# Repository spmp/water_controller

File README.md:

Water Controller
================

The aim of this project is to control and monitor a water heating system.
This is currently a **Work in Progress**, and it is largely incomplete.

The project will consist of four main parts:

  1. An atmega328 MCU with a control system that directly interfaces with
     the water heater. It also operates over a serial interface to interact
     with a PC.

  2. A daemon running on the PC which can talk to the MCU. The daemon receives
     regular logging information from the MCU which it saves to a database.
     The daemon also allows various commands to be sent to the MCU.

  3. A web application that can display logs from the database, and can
     control the MCU via the daemon.
     
  4. A schematic and PCB artwork.

Currently only (1) is functional.

The _driveres_ for the project are in `AVR-lib`. At this stage I am (slowly) moving to github for issue tracking etc.

MCU
---

The project uses the Arduino Nano for both prototyping and target operation. To upload the code do the following:

 1. Plug in the MCU via USB to your computer. Check that `lsusb` shows the
    device, and that /dev/ttyUSB0 is writable (add your user to that device's
    group if not).

 2. Install the avr gcc toolchain. In Ubuntu/Debian, the packages you need
    (at least) are `avr-gcc`, `avr-libc`, and `avrdude` and their
    dependencies.

 3. Run `make` to compile the source, and `make upload` to compile and upload
    to the MCU via `/dev/ttyUSB*`. The program will start running immediately.

At present, the MCU reads data from the following inputs:

 * Pressure sensor (MPXV4006 I think...) via 12 bit I2C ADC (MPXV4006)
 * Temperature sensors (DS18B20) via OW to I2C (DS2482-100) (WIP)

These are sent over the serial interface to the PC along with a "timestamp" (the
number of seconds since the program started) at regular intervals.

To view the output, run `screen /dev/ttyUSB0 38400` (exit with `C-a k y`).

Logging daemon (logger.py)
--------------------------

This saves the data sent from the MCU to a sqlite3 database. Written in
Python3. To run it, just run

    $ ./logger.py

when the MCU is connected to the computer. The program will print out the
messages it recieves from the MCU, and also insert them into the database
`log_timeseries.db`. Type `Ctrl-C` or `Ctrl-D` to exit. You can view the
database directly using `sqlite3 log_timerseries.db`.

The logger should also have an interface for sending commands to the MCU. The
interface will be over TCP or a named pipe.

Web interface
-------------

The backend of the web layer reads from the sqlite3 database and displays
useful graphs on a web page. The graphs are rendered client-side using
jqplot, a jquery plugin. All of the javascript libraries are accessed over
cdn, meaning they don't have to be stored on the web server.

The backend is written in Python3, and uses the [Bottle web framework][bottle].
Bottle is a WSGI compliant framework, so it can be used with apache or nginx.
It can also run on its own using the builtin Python WSGIServer. This is the
current setup, and it can be run using

    $ web/webapp.py

where it serves the files to localhost:8080.

[bottle]: http://bottlepy.org/docs/stable/

The web page should also contain some commands to directly control the MCU.
These will be sent via the web backend to the logging daemon and from there
on to the MCU.

Circuit
-------

In brief: The Arduino nano plugs into the circuit board, reads its inputs from I2C, sending serial out via a MAX232. The heaters and pump are controlled via zero crossing triac driver and triacs. The filler solenoid is controlled via logic level fet. All outputs can be disabled, overwridden, or be controlled via MCU with a three position toggle switch. LED's indicate the output state, and the MCU flashes politely when operating. DC power is supplied by a 12V smps.

The circuit and artwork are in ```cad``` and ```eagle``` respectivly.

Issues
------
* The I2C driver needs a major upate which must happen in tandem with this (and all other dependent projects) to support a separate error state with recovery.
* If an I2C error in level is detected it must:
    1. Report 0mm
    2. Turn off heaters
    3. Turn off filler
    4. Turn off pump
    5. Raise a _level_ error flag in USART output
    
* If an error in temperature is detected it must:
    1. Report 0deg cent.
    2. Turn off heater
    3. Raise a _temperature_ error flag in USART output
    
Normal operation must continue once normal sensing is restored.

* Fill time detection and auto off. Sometimes the filler does not turn off correctl due to I2C errors or misreading. To avoid a flooded yard whilst on holiday a maximum fill time needs to be obeyed, taking into account a complete fill _with_ the pump on. If this time (`MAX_FILL_TIME`) is exceeded the filler must be disabled and not re-enabled unless done so manually via USART.

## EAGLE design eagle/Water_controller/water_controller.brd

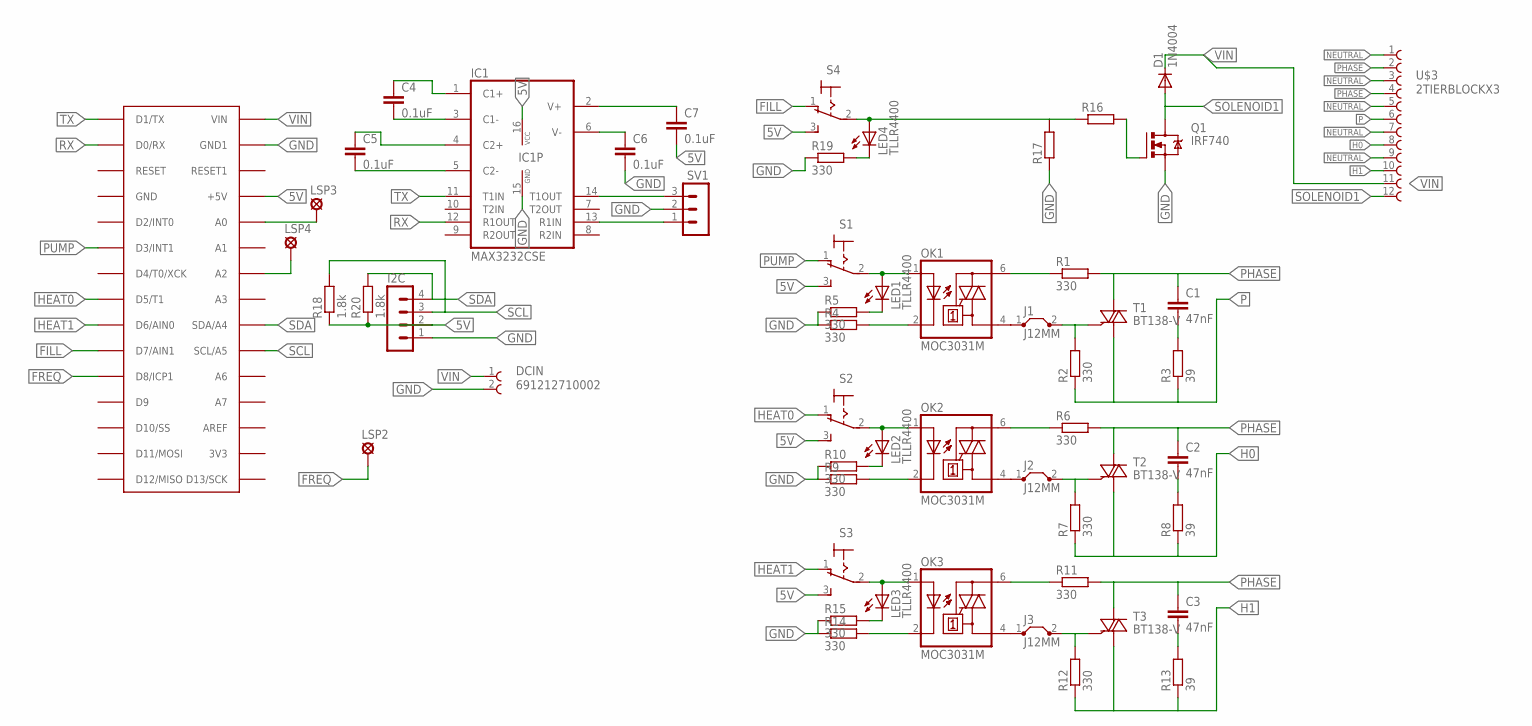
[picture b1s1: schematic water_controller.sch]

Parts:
C1, C2, C3: 47nF; C150-064X183
C4, C5, C6, C7: 0.1uF; C0805
D1: 1N4004; DO41-10
DCIN: 691212710002
I2C: MA04-1
IC1: MAX3232CSE; SO16
J1, J2, J3: J12MM; 12
LED1, LED2, LED3, LED4: TLLR4400; LED3MM
LSP2, LSP3, LSP4: LSP11
OK1, OK2, OK3: MOC3031M; DIL06; MPN MOC3063
Q1: IRF740; TO220BV
R1, R2, R6, R7, R11, R12: 330; M1206
R3, R8, R13: 39; M1206
R4, R5, R9, R10, R14, R15, R19: 330; R1206
R16: R-EU_0204/7; 0204/7
R17: R-EU_M1206; M1206
R18, R20: 1.8k; R1206
S1, S2, S3, S4: M9040P
SV1: MA03-1
T1, T2, T3: BT138-V; TO220BV
U$1: ARDUINONANO; PDIP-32
U$3: 2TIERBLOCKX3; 2TIERX3

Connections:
5V: C7.2, I2C.2, IC1.16 (VCC), R18.1, R20.1, S1.3 (S), S2.3 (S), S3.3 (S), S4.3 (S), U$1.+5V
FILL: S4.1 (O), U$1.D7 (D7/AIN1)
FREQ: LSP2.MP, U$1.D8 (D8/ICP1)
GND: C6.2, DCIN.2, I2C.1, IC1.15 (GND), Q1.S, R4.1, R5.1, R9.1, R10.1, R14.1, R15.1, R17.1, R19.1, SV1.2, U$1.GND1
H0: R7.1, R8.1, T2.T1 (A1), U$3.8
H1: R12.1, R13.1, T3.T1 (A1), U$3.10
HEAT0: S2.1 (O), U$1.D5 (D5/T1)
HEAT1: S3.1 (O), U$1.D6 (D6/AIN0)
unnamed: C1.2, R3.2
unnamed: C2.2, R8.2
unnamed: OK1.6 (A2), R1.1
unnamed: J1.2, R2.2, T1.G
unnamed: C4.2, IC1.3 (C1-)
unnamed: OK1.2 (C), R4.2
unnamed: LED1.A, OK1.1 (A), S1.2
unnamed: LED1.K (C), R5.2
unnamed: C4.1, IC1.1 (C1+)
unnamed: OK2.6 (A2), R6.1
unnamed: J2.2, R7.2, T2.G
unnamed: OK2.2 (C), R9.2
unnamed: LED2.A, OK2.1 (A), S2.2
unnamed: LED2.K (C), R10.2
unnamed: C3.2, R13.2
unnamed: OK3.6 (A2), R11.1
unnamed: J3.2, R12.2, T3.G
unnamed: OK3.2 (C), R14.2
unnamed: LED3.A, OK3.1 (A), S3.2
unnamed: LED3.K (C), R15.2
unnamed: C5.2, IC1.5 (C2-)
unnamed: Q1.G, R16.2
unnamed: C5.1, IC1.4 (C2+)
unnamed: LED4.A, R16.1, R17.2, S4.2
unnamed: LED4.K (C), R19.2
unnamed: C6.1, IC1.6 (V-)
unnamed: C7.1, IC1.2 (V+)
unnamed: J1.1, OK1.4 (A1)
unnamed: J2.1, OK2.4 (A1)
unnamed: J3.1, OK3.4 (A1)
unnamed: IC1.13 (R1IN), SV1.1
unnamed: IC1.14 (T1OUT), SV1.3
unnamed: LSP4.MP, U$1.A2
unnamed: LSP3.MP, U$1.A0
NEUTRAL: U$3.1, U$3.3, U$3.5, U$3.7, U$3.9
P: R2.1, R3.1, T1.T1 (A1), U$3.6
PHASE: C1.1, C2.1, C3.1, R1.2, R6.2, R11.2, T1.T2 (A2), T2.T2 (A2), T3.T2 (A2), U$3.2, U$3.4
PUMP: S1.1 (O), U$1.D3 (D3/INT1)
RX: IC1.12 (R1OUT), U$1.D0/RX
SCL: I2C.3, R18.2, U$1.A5 (SCL/A5)
SDA: I2C.4, R20.2, U$1.A4 (SDA/A4)
SOLENOID1: D1.A, Q1.D, U$3.12
TX: IC1.11 (T1IN), U$1.D1/TX
VIN: D1.C, DCIN.1, U$1.VIN, U$3.11

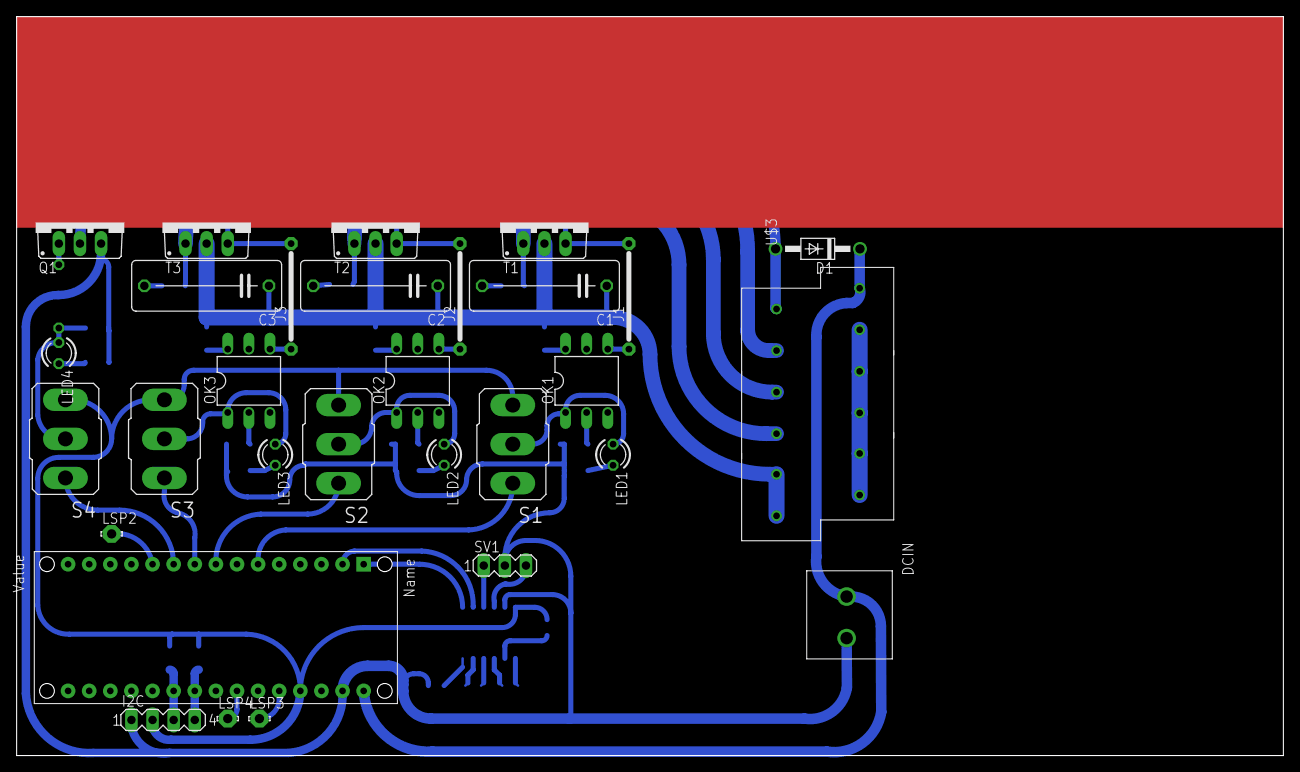
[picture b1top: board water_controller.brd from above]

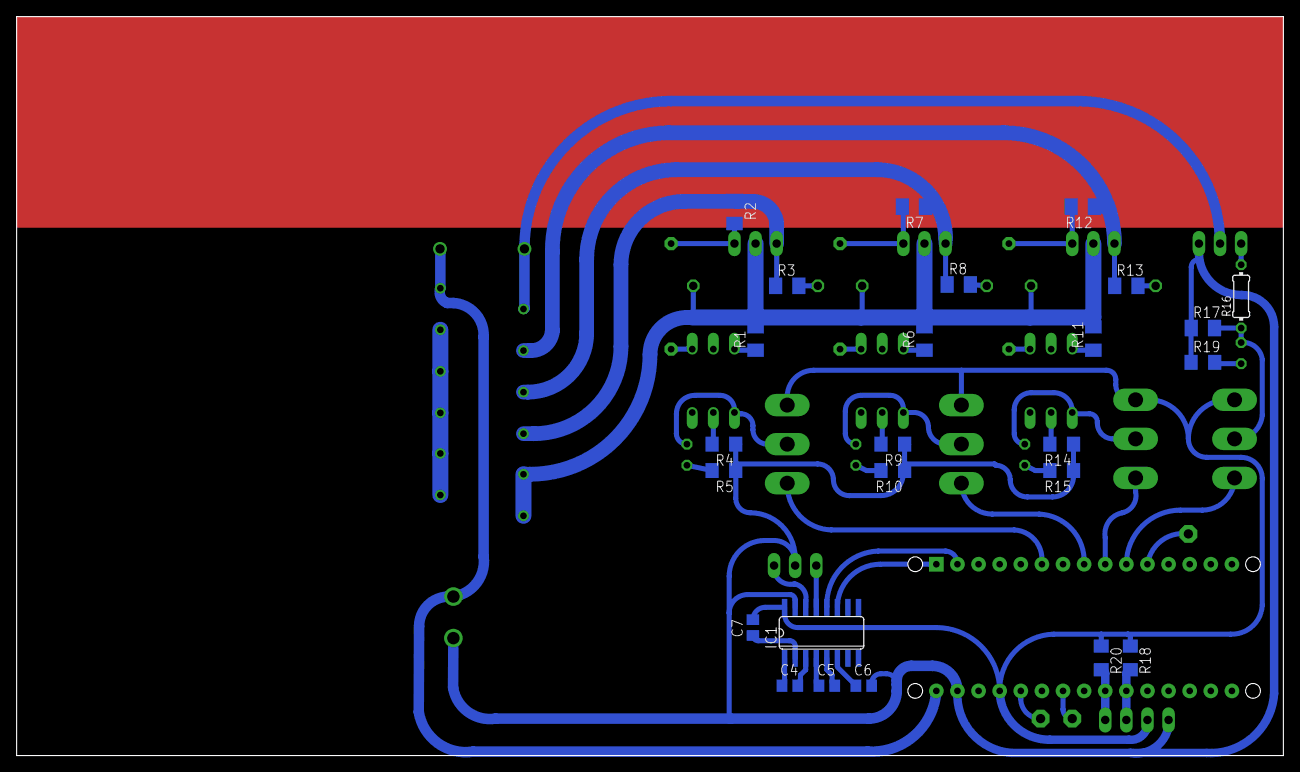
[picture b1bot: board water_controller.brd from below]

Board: 2 copper layers, 152.4 x 88.9 mm, 55 parts (25 on the bottom side), 52 nets.

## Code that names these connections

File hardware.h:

#pragma once
#include <avr/io.h>

/* AVR specifics */
#include "AVR-lib/clock.h"
#include "AVR-lib/ds18x20.h"
#include "AVR-lib/i2c_safe.h"
#include "AVR-lib/usart.h"
#include "AVR-lib/wd.h"
#include "state-machine.h"

/* DEBUGGING - i.e no environmental measurements */
// #define DEBUGGING

/* State machine defaults */
#define STATEMACHINEENABLEDONSTART 1
#define LOGGINGENABLEDONSTART 1
#define HEATERENABLEDONSTART 1
#define ANALYTICSENABLEDONSTART 1

/* Fill timer */
#define FILL_MAX_TIME 900
#define FILL_CHECK_TIME 60

/* Heater size */
#define HEATER_SIZE     2400L
#define SPECIFIC_HEAT_WATER 4186L

/* Clock and timing settings, time in 1/125's of a second*/
#define LONG_TIME_INTERVAL          CLOCK_TICKS_PER_SECOND*600L

/* Inputs */
#include "temperature.h"//Temperature reading
#include "level.h"      //Level and volume reading

/* Data buss settings   */
// USART
#define USARTBAUD       38400
// I2C
#define I2CSPEED        1000
// OW bit bang
#define OWPIN           PB0
#define OWIN            PINB
#define OWOUT           PORTB
#define OWDDR           DDRB
#define OW_USE_INTERNAL_PULLUP     0

// ds18x20 defines
#define DS18X20TEMPRES  DS18B20_12_BIT 

// IO defines:
#define ONBOARD_LED     PB5

#define OUTPUT_PORT     PORTD
#define INPUT_PORT      PIND
#define DIRECTION_REG   DDRD
#define PUMP_PIN        PD3
#define FILL_PIN        PD7
#define HEAT1_PIN       PD5
#define HEAT2_PIN       PD6

/* Initialise all hardware relevant to the project, usart, i2c, clock, external
 * sensors, Everyting!
 * One call to rule them all */
void init_hardware(struct Program *program);

/* Initialise I/O ports on the AVR */
void init_io_ports(void);

/* Hardware states */
uint8_t pump_state(void);
uint8_t fill_state(void);
uint8_t heater_state(void);

/* Set hardware states */
void pump_set(uint8_t state);
void fill_set(uint8_t state);
void heater_set(uint8_t state);

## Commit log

2013-11-02 Add clock using timer/counter 2
2013-11-02 log ultrasonic & analog inputs to serial with timestamp
2013-11-02 simplify the ultrasonic distance measure
    The ultrasonic measurer now uses a single I/O pin (PORTB0/ardiuno digital 8)
    and a single interrupt (TIMER1_CAPT). When the ultrasonic sensor is not in
    use, TIMER1 is free for use in other parts of the application.
2013-11-02 add informative README.md
2013-11-07 Add logger and basic web interface that displays graphs from the micro.
2013-11-30 Modified ADC read_analog for the case of pin 8 being internal temp. Spun off ADC stuff to adc.{c,h} Added very basic frequqncy measurement using 16 input capture timer Modified main - removed ultraso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
2013-12-08 Cleaned up as per *useful* comments. Added temperature related things. Maybe fixed frequency counter.
2014-01-14 Levels and things, usart recieve and parse. Hardware will change
2014-01-14 Tidy up recieving commands and the core program loop.
2014-01-15 Move code around mostly, having trouble compiling - multiple definition of 'read_inputs_flag'.
2014-01-20 Hardware: Schematic and PCB artwork done.
2014-02-18 i2c working with safe high level commands -- still need to find a way to break out of read_ack and read_nak while loop. Logging in separate folder. The idea of a config.h not sure how to impliment wi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
2014-02-18 Fixed dependency issues, some more stuff in command to test temperature probe.. all good. Need to get this whole struct input blah thing sorted so can get some good log messages.. Anyone want to fini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
2014-02-21 Defined two more time periods: medium and fast, set state machine to run in medium tome perod, and separated USART, statemachine and logging, such that they are indipendent and USART and logging are 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
2014-02-26 Wow, a Version 1.0alpha! Should be a working system _when_ program is populated with values... still to be done. Lots and lots to do... oh so much for a project that was supposed to take two weeks. N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
2014-03-03 A working version with no 'state machine' for now. Added new functions to usart for uint32 and half uint32. Changed uint and i2c_safe init such that speed/baude and f_cpu are parameters. Changed the 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
2014-03-03 loads of floating point stuff sorted, volume and level fixed with zeroing routine. Fill routine faulty. redo with a ton of if thens
2014-03-06 Stuff, and the attempt to have multiple programs as program[], failing to initialise the programs so will revert on the next commit. Floating point done. Progmem done, hence USART menu (command.c) do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
2014-08-12 Fixing broken heater logic. Clunky but obvious code
2014-08-13 fixed a lot of the temperature and heating stuff. Linearly approximating volume to avoid floating point
2014-08-13 Test of various level/volume/heating related stuff.
2014-08-15 moving to another computer. Need to fix probe.. again
2014-08-18 Added basic morning fill logic. Updated I2C address of one temperature sensor
2014-08-19 moving from BaaBaaBlacksheep for level testing
2014-08-19 Recalibrate level sensor, revert Volume to floating point version
2014-09-08 BaaBaaBlacksheep: Add watchdog initialisation and reset (after logging message). Add initialisation serial string.
2014-09-08 Attempting to fix watchdog lockout
2014-09-10 added prefix's and suffixes to command.c usart output. Code is HORRID and needs to be written nicely some time in the future- reuse etc..
2014-09-10 Fixed overflow in temperature by increasing size of read_AT30TSE758 to int32, whilst keeping temperature at uint16 as assue its not negative. Note there is a multiplication by 125 in read_AT30TSE758,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
2014-10-08 Dunno where, from BaaBaa
2014-10-08 Rudimentary watchdog reset after 4S implimented. Added variable 'mcusr_mirror' in attempt to catch reset source, not working, or else always 0
2014-10-09 Added proper reset testing using Optiboot internals 'r2'. ABout to start breaking IIC
2014-10-09 Properly made safe the i2c routines with uint16 counters. Need to add failure mode detection...
2014-11-03 Fixing temperature issues. Signed and unsignedmake clean && make && make upload! Changed temperature to unsigned 16bit, so is Cx100
2014-12-02 New temperature sensors and more stuff
2014-12-13 command and pressure sensor calibration mk II
2016-02-06 Ensuring that AVR-lib libraries are used
2016-02-07 Updated heaps of stuff to use new temperature sensor. Temperature is now a int32 throughout.
2016-02-07 Update TODO.md and version
2016-02-08 make timetoHot more explicit. Fix terminal output for temperature. Add verion define and incriment
2016-02-19 Added a maximum fill time check with associate error register and 'setters and getters' from command
2016-02-19 Fix 'howlong' calculation. Add debugging support, i.e manually enter temperature with 'T' and level with 'l'
2016-02-19 Update to use clock.h and wd.h from AVR-lib
2016-02-21 is working which it wasnt
2016-02-21 First cut of cumulative energy implimentation
2016-02-22 Tested anaytics with correct timezone. Fixed analytics enable logic
2016-02-22 Add analytics enable/disable from command.c
2016-02-22 OOps add analytics.{c,h}
2016-02-27 Add extra check for filling if no increase from zero. Add option to adjust analytics time
2016-02-27 Increase default analytics time
2016-02-27 Updated and fixed fill testing, will now error if level does not increase.

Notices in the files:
parts and their libraries:
ZugbuegelsystemWR-TBL: Copyright: Würth Elektronik
